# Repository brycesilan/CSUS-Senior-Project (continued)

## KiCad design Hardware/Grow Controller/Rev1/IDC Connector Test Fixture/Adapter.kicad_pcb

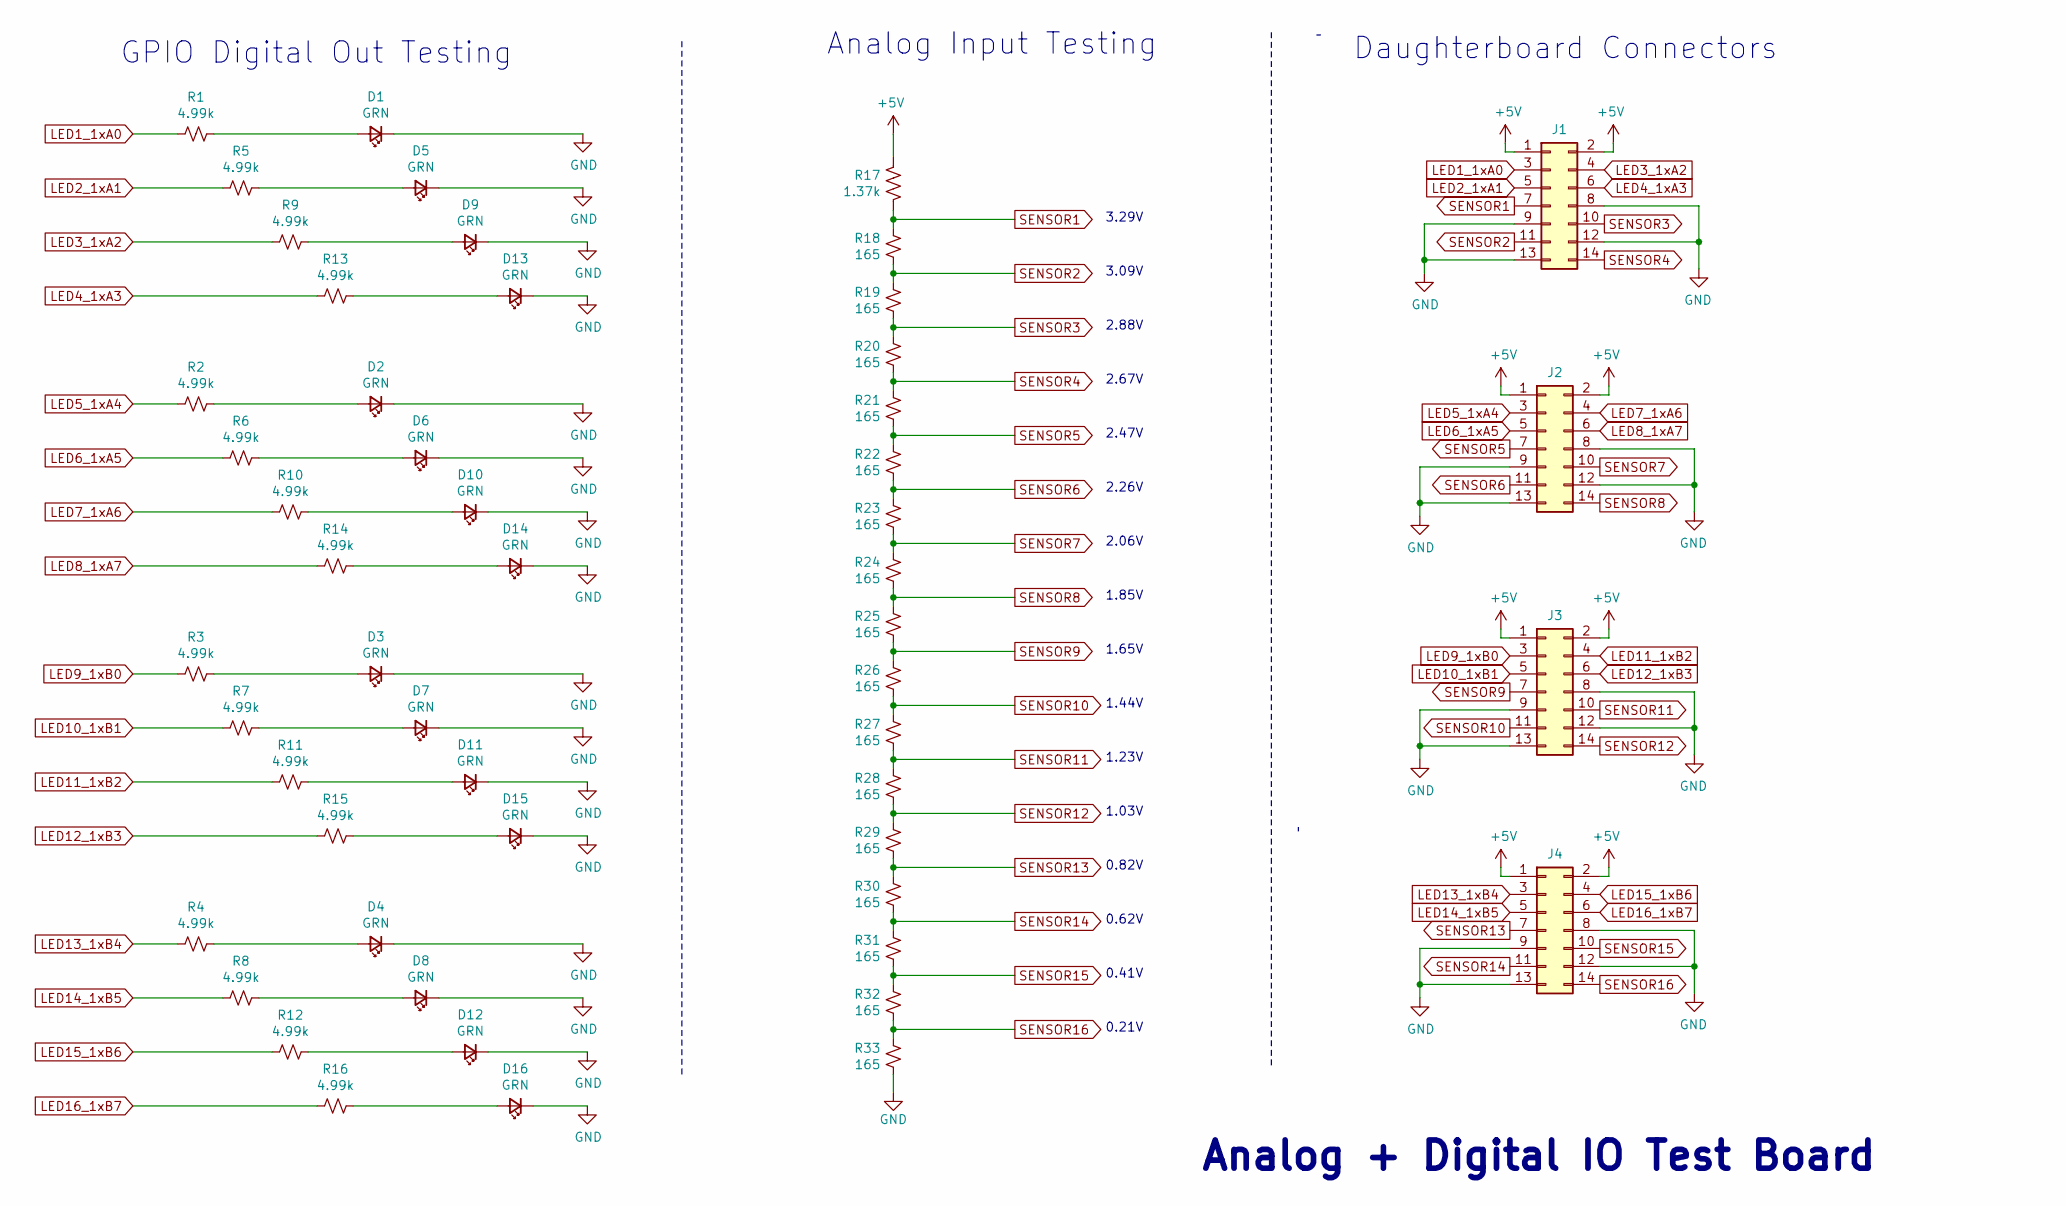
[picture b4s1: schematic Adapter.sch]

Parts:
D1, D2, D3, D4, D5, D6, D7, D8, D9, D10, D11, D12, D13, D14, D15, D16: GRN; D_0603_1608Metric
J1, J2, J3, J4: Conn_02x07_Odd_Even; PinHeader_2x07_P2.54mm_Vertical
R1, R2, R3, R4, R5, R6, R7, R8, R9, R10, R11, R12, R13, R14, R15, R16: 4.99k; R_0603_1608Metric
R17: 1.37k; R_0603_1608Metric
R18, R19, R20, R21, R22, R23, R24, R25, R26, R27, R28, R29, R30, R31, R32, R33: 165; R_0603_1608Metric

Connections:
+5V: J1.1, J1.2, J2.1, J2.2, J3.1, J3.2, J4.1, J4.2, R17.1
GND: D1.1 (K), D2.1 (K), D3.1 (K), D4.1 (K), D5.1 (K), D6.1 (K), D7.1 (K), D8.1 (K), D9.1 (K), D10.1 (K), D11.1 (K), D12.1 (K), D13.1 (K), D14.1 (K), D15.1 (K), D16.1 (K), J1.8, J1.9, J1.12, J1.13, J2.8, J2.9, J2.12, J2.13, J3.8, J3.9, J3.12, J3.13, J4.8, J4.9, J4.12, J4.13, R33.2
LED1_1xA0: J1.3, R1.2
LED2_1xA1: J1.5, R5.2
LED3_1xA2: J1.4, R9.2
LED4_1xA3: J1.6, R13.2
LED5_1xA4: J2.3, R2.2
LED6_1xA5: J2.5, R6.2
LED7_1xA6: J2.4, R10.2
LED8_1xA7: J2.6, R14.2
LED9_1xB0: J3.3, R3.2
LED10_1xB1: J3.5, R7.2
LED11_1xB2: J3.4, R11.2
LED12_1xB3: J3.6, R15.2
LED13_1xB4: J4.3, R4.2
LED14_1xB5: J4.5, R8.2
LED15_1xB6: J4.4, R12.2
LED16_1xB7: J4.6, R16.2
unnamed: D1.2 (A), R1.1
unnamed: D2.2 (A), R2.1
unnamed: D3.2 (A), R3.1
unnamed: D4.2 (A), R4.1
unnamed: D5.2 (A), R5.1
unnamed: D6.2 (A), R6.1
unnamed: D7.2 (A), R7.1
unnamed: D8.2 (A), R8.1
unnamed: D9.2 (A), R9.1
unnamed: D10.2 (A), R10.1
unnamed: D11.2 (A), R11.1
unnamed: D12.2 (A), R12.1
unnamed: D13.2 (A), R13.1
unnamed: D14.2 (A), R14.1
unnamed: D15.2 (A), R15.1
unnamed: D16.2 (A), R16.1
SENSOR1: J1.7, R17.2, R18.1
SENSOR2: J1.11, R18.2, R19.1
SENSOR3: J1.10, R19.2, R20.1
SENSOR4: J1.14, R20.2, R21.1
SENSOR5: J2.7, R21.2, R22.1
SENSOR6: J2.11, R22.2, R23.1
SENSOR7: J2.10, R23.2, R24.1
SENSOR8: J2.14, R24.2, R25.1
SENSOR9: J3.7, R25.2, R26.1
SENSOR10: J3.11, R26.2, R27.1
SENSOR11: J3.10, R27.2, R28.1
SENSOR12: J3.14, R28.2, R29.1
SENSOR13: J4.7, R29.2, R30.1
SENSOR14: J4.11, R30.2, R31.1
SENSOR15: J4.10, R31.2, R32.1
SENSOR16: J4.14, R32.2, R33.1

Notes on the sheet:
Daughterboard Connectors
GPIO Digital Out Testing
Analog Input Testing
3.09V
3.29V
2.88V
2.67V
2.47V
2.26V
1.85V
2.06V
1.65V
1.44V
1.23V
1.03V
0.62V
0.82V
0.41V
0.21V
Analog + Digital IO Test Board

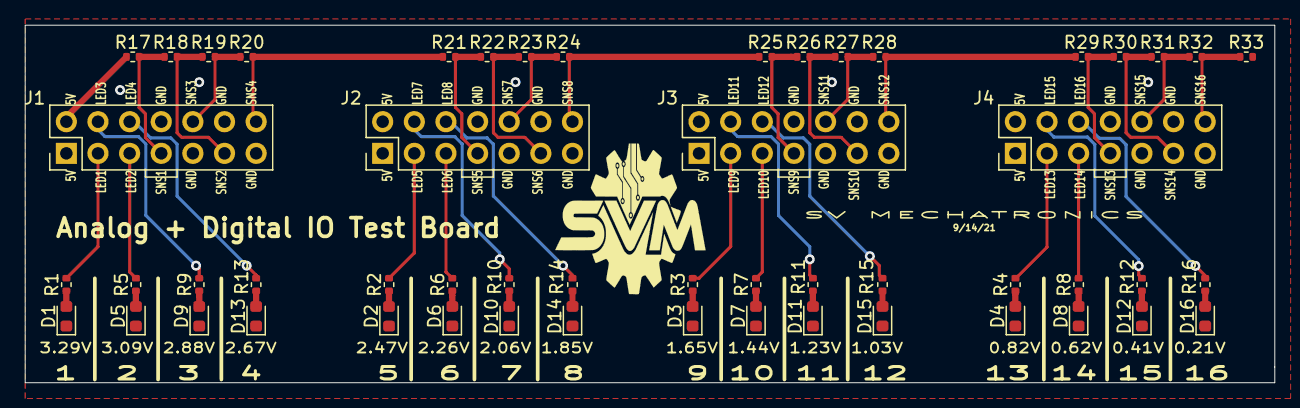
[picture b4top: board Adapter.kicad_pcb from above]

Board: 2 copper layers, 100.3 x 28.7 mm, 53 parts (0 on the bottom side), 50 nets.

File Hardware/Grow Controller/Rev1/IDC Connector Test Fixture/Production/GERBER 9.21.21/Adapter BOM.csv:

Comment,Designator,Footprint,LCSC Part Number
Green LED_0603,"D1,D2,D3,D4,D5,D6,D7,D8,D9,D10,D11,D12,D13,D14,D15,D16",D_0603,
4.99k,"R1,R2,R3,R4,R5,R6,R7,R8,R9,R10,R11,R12,R13,R14,R15,R16",R_0603,
1.37k,R17,R_0603,
165,"R18,R19,R20,R21,R22,R23,R24,R25,R26,R27,R28,R29,R30,R31,R32,R33",R_0603,

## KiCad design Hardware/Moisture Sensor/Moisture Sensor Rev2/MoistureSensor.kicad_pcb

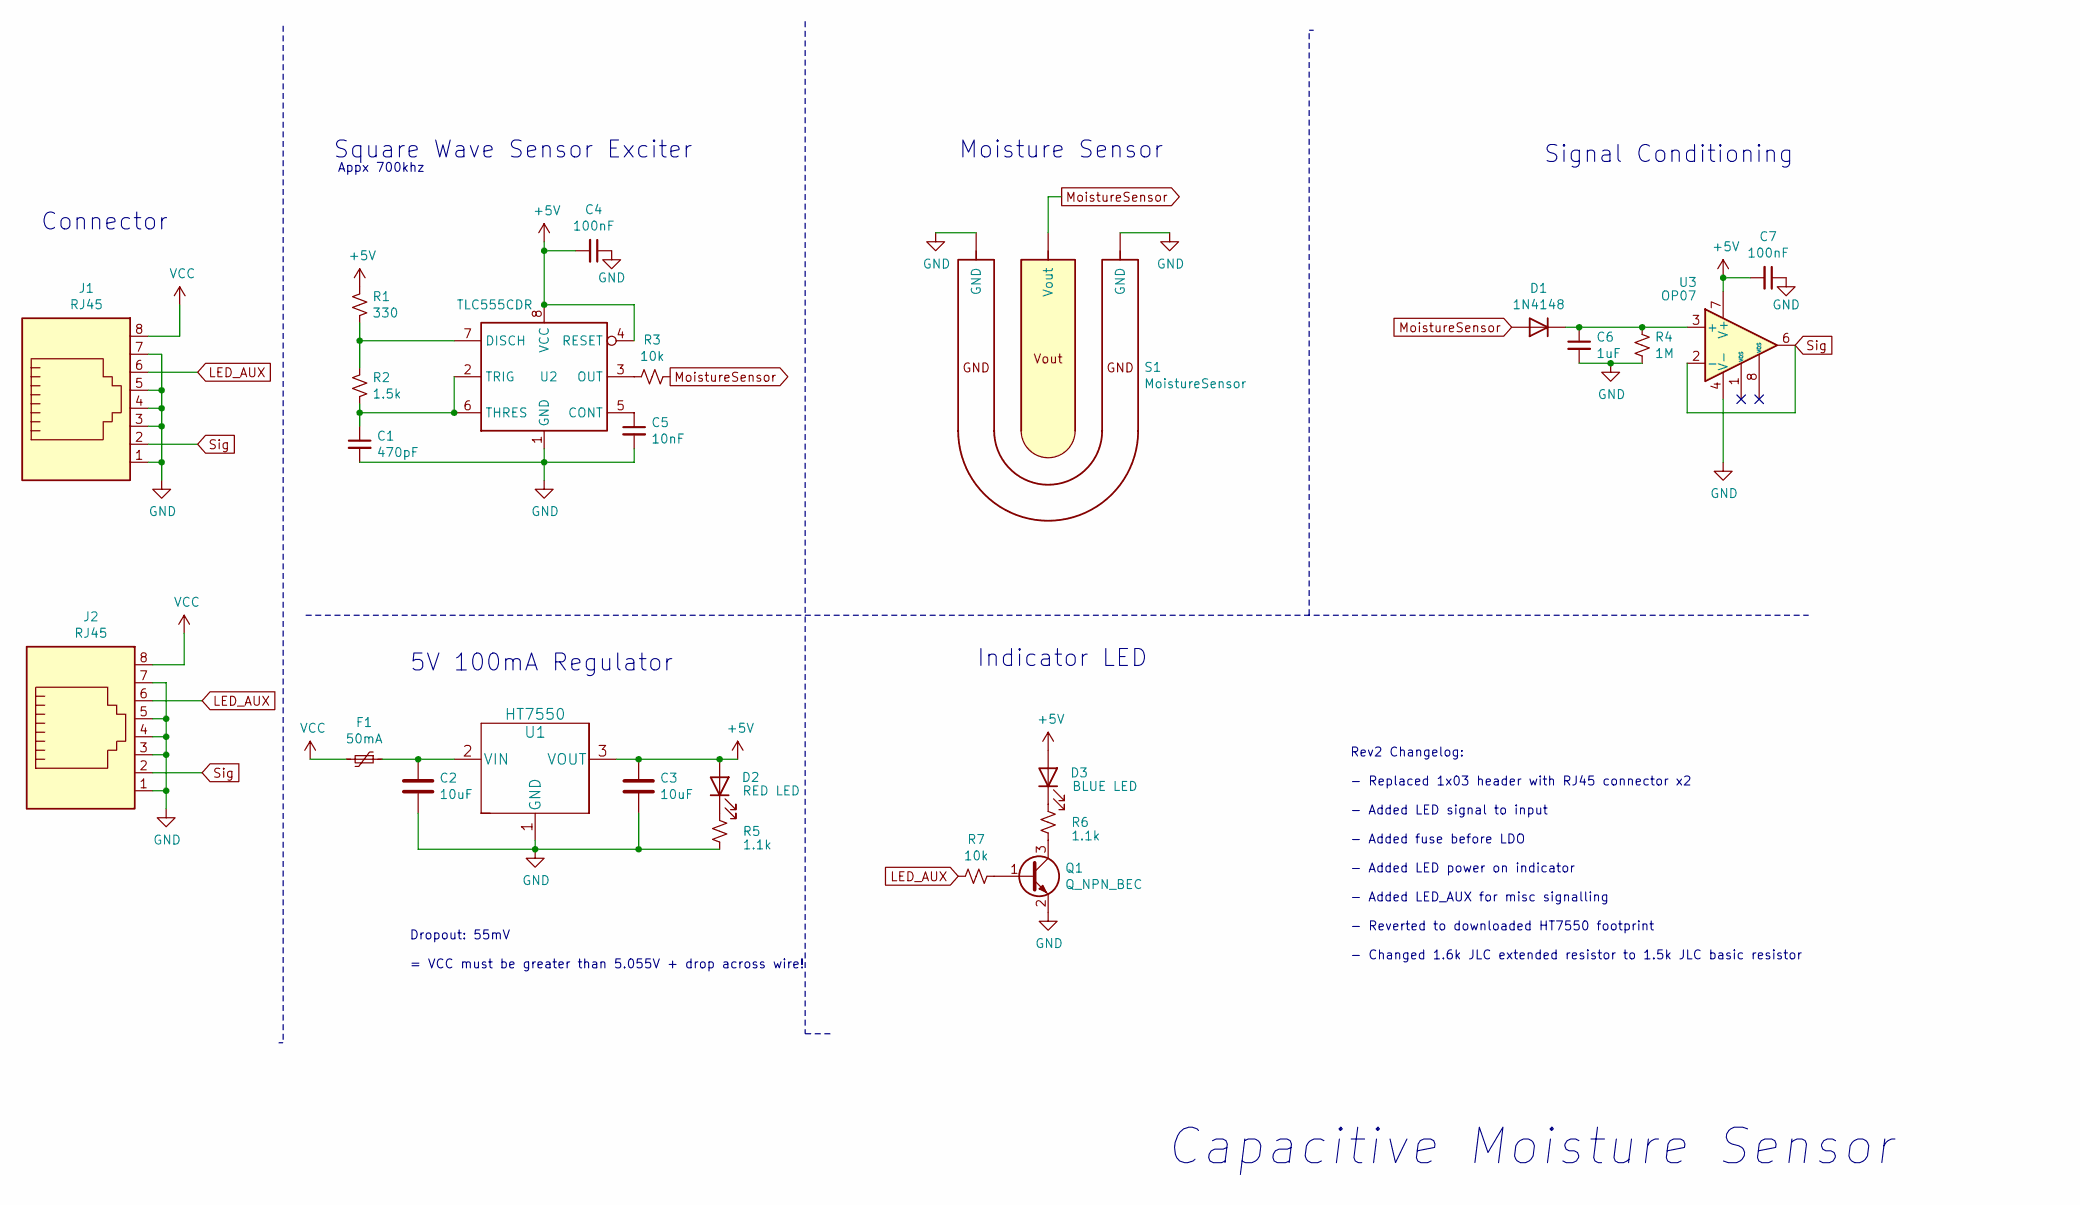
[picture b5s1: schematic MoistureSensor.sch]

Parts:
C1: 470pF; C_0402_1005Metric
C2, C3: 10uF; C_0805_2012Metric
C4, C7: 100nF; C_0402_1005Metric
C5: 10nF; C_0402_1005Metric
C6: 1uF; C_0603_1608Metric
D1: 1N4148; D_SOD-323F
D2: RED LED; LED_0805_2012Metric
D3: BLUE LED; LED_0805_2012Metric
F1: 50mA; Fuse_1206_3216Metric
J1, J2: RJ45; AMPHENOL_54602-908LF
Q1: Q_NPN_BEC; SOT-23
R1: 330; R_0402_1005Metric
R2: 1.5k; R_0402_1005Metric
R3, R7: 10k; R_0402_1005Metric
R4: 1M; R_0402_1005Metric
R5, R6: 1.1k; R_0603_1608Metric
S1: MoistureSensor
U1: HT7550; HT7550-1-SOT89TRLF
U2: TLC555CDR; SOIC-8_3.9x4.9mm_P1.27mm
U3: OP07; SOIC-8_3.9x4.9mm_P1.27mm

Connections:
+5V: C3.1, C4.2, C7.2, D2.2 (A), D3.2 (A), R1.1, U1.3 (VOUT), U2.4 (RESET), U2.8 (VCC), U3.7 (V+)
GND: C1.2, C2.2, C3.2, C4.1, C5.2, C6.2, C7.1, J1.1, J1.3, J1.4, J1.5, J1.7, J2.1, J2.3, J2.4, J2.5, J2.7, Q1.2 (E), R4.2, R5.2, S1.1 (GND), S1.3 (GND), U1.1 (GND), U2.1 (GND), U3.4 (V-)
LED_AUX: J1.6, J2.6, R7.2
MoistureSensor: D1.2 (A), R3.1, S1.2 (Vout)
unnamed: C1.1, R2.2, U2.2 (TRIG), U2.6 (THRES)
unnamed: C2.1, F1.1, U1.2 (VIN)
unnamed: C5.1, U2.5 (CONT)
unnamed: C6.1, D1.1 (K), R4.1, U3.3 (+)
unnamed: D2.1 (K), R5.1
unnamed: D3.1 (K), R6.1
unnamed: Q1.1 (B), R7.1
unnamed: Q1.3 (C), R6.2
unnamed: R1.2, R2.1, U2.7 (DISCH)
unnamed: R3.2, U2.3 (OUT)
Sig: J1.2, J2.2, U3.2 (-), U3.6
VCC: F1.2, J1.8, J2.8

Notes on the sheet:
Appx 700khz
Square Wave Sensor Exciter
Moisture Sensor
Signal Conditioning
5V 100mA Regulator
Connector
Dropout: 55mV = VCC must be greater than 5.055V + drop across wire!
Rev2 Changelog: - Replaced 1x03 header with RJ45 connector x2 - Added LED signal to input - Added fuse before LDO - Added LED power on indicator - Added LED_AUX for misc signalling - Reverted to downloaded HT7550 footprint - Changed 1.6k JLC extended resistor to 1.5k JLC basic resistor
Indicator LED
Capacitive Moisture Sensor

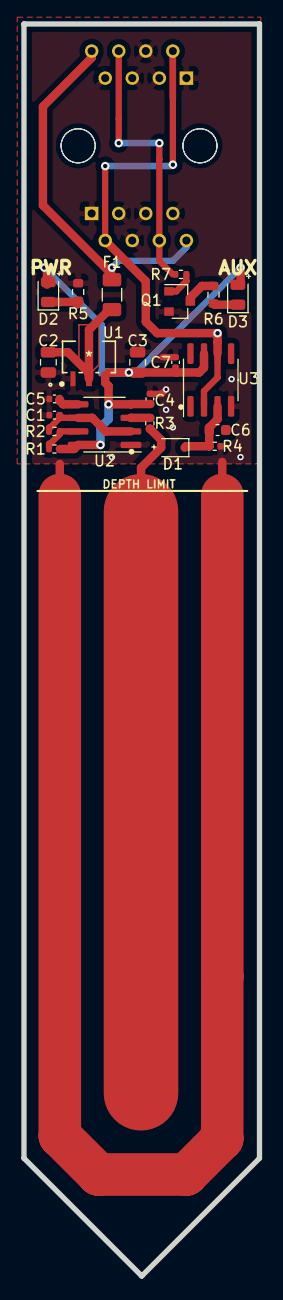
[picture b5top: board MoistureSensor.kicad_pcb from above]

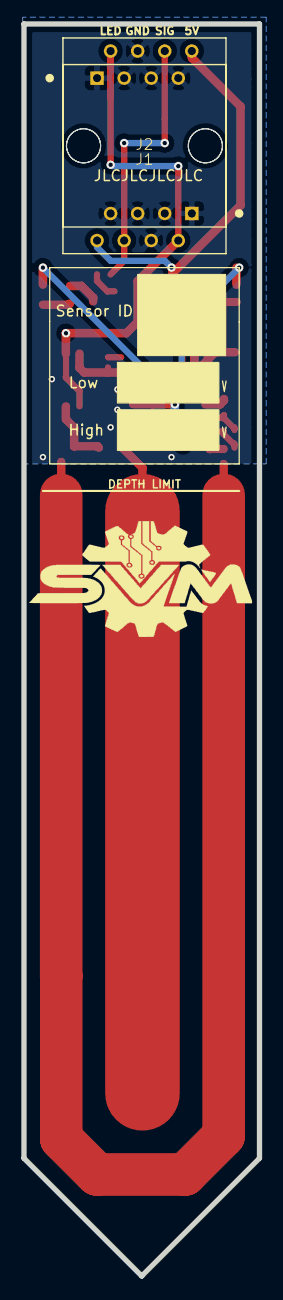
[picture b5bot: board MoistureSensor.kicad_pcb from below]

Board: 2 copper layers, 22.1 x 117.5 mm, 24 parts (2 on the bottom side), 16 nets.

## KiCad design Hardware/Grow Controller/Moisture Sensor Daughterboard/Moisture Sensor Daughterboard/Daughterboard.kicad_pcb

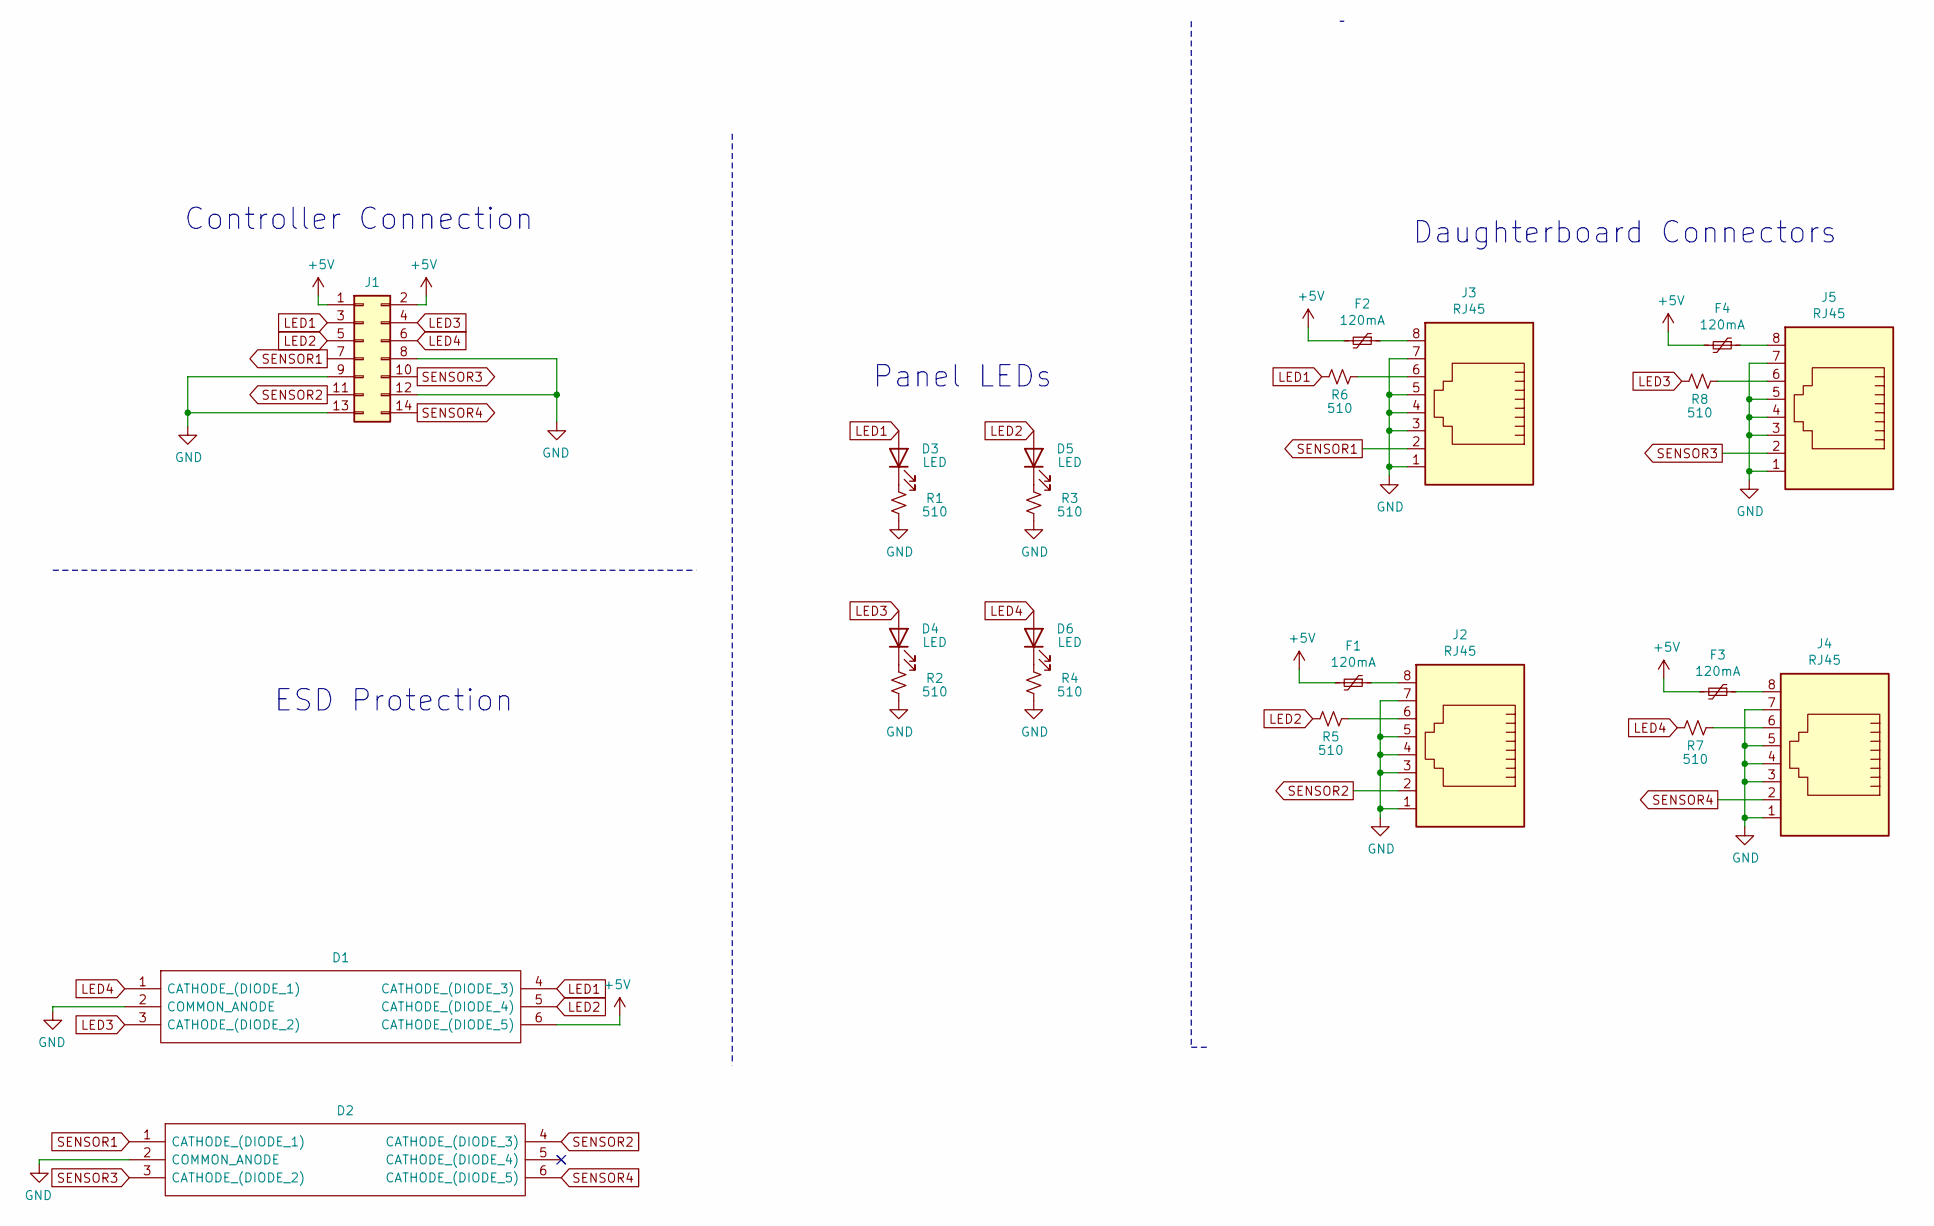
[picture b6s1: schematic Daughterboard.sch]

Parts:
D1, D2: PESD5V0L5UV,115; SOTFL50P160X60-6N; Manufacturer_Part_Number PESD5V0L5UV,115; Mouser Part Number 771-PESD5V0L5UV115
D3, D4, D5, D6: LED; LED_0805_2012Metric
F1, F2, F3, F4: 120mA; Fuse_0603_1608Metric_Pad1.05x0.95mm_HandSolder
J1: Conn_02x07_Odd_Even; IDC-Header_2x07_P2.54mm_Latch_Vertical
J2, J3, J4, J5: RJ45; RJ45_OST_PJ012-8P8CX_Vertical
R1, R2, R3, R4, R5, R6, R7, R8: 510; R_0805_2012Metric

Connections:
+5V: D1.6 (CATHODE_(DIODE_5)), F1.2, F2.2, F3.2, F4.2, J1.1, J1.2
GND: D1.2 (COMMON_ANODE), D2.2 (COMMON_ANODE), J1.8, J1.9, J1.12, J1.13, J2.1, J2.3, J2.4, J2.5, J2.7, J3.1, J3.3, J3.4, J3.5, J3.7, J4.1, J4.3, J4.4, J4.5, J4.7, J5.1, J5.3, J5.4, J5.5, J5.7, R1.1, R2.1, R3.1, R4.1
LED1: D1.4 (CATHODE_(DIODE_3)), D3.2 (A), J1.3, R6.2
LED2: D1.5 (CATHODE_(DIODE_4)), D5.2 (A), J1.5, R5.2
LED3: D1.3 (CATHODE_(DIODE_2)), D4.2 (A), J1.4, R8.2
LED4: D1.1 (CATHODE_(DIODE_1)), D6.2 (A), J1.6, R7.2
unnamed: D3.1 (K), R1.2
unnamed: D4.1 (K), R2.2
unnamed: D5.1 (K), R3.2
unnamed: D6.1 (K), R4.2
unnamed: F1.1, J2.8
unnamed: F2.1, J3.8
unnamed: F3.1, J4.8
unnamed: F4.1, J5.8
unnamed: J2.6, R5.1
unnamed: J3.6, R6.1
unnamed: J4.6, R7.1
unnamed: J5.6, R8.1
SENSOR1: D2.1 (CATHODE_(DIODE_1)), J1.7, J3.2
SENSOR2: D2.4 (CATHODE_(DIODE_3)), J1.11, J2.2
SENSOR3: D2.3 (CATHODE_(DIODE_2)), J1.10, J5.2
SENSOR4: D2.6 (CATHODE_(DIODE_5)), J1.14, J4.2

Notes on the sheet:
Daughterboard Connectors
Controller Connection
Panel LEDs
ESD Protection

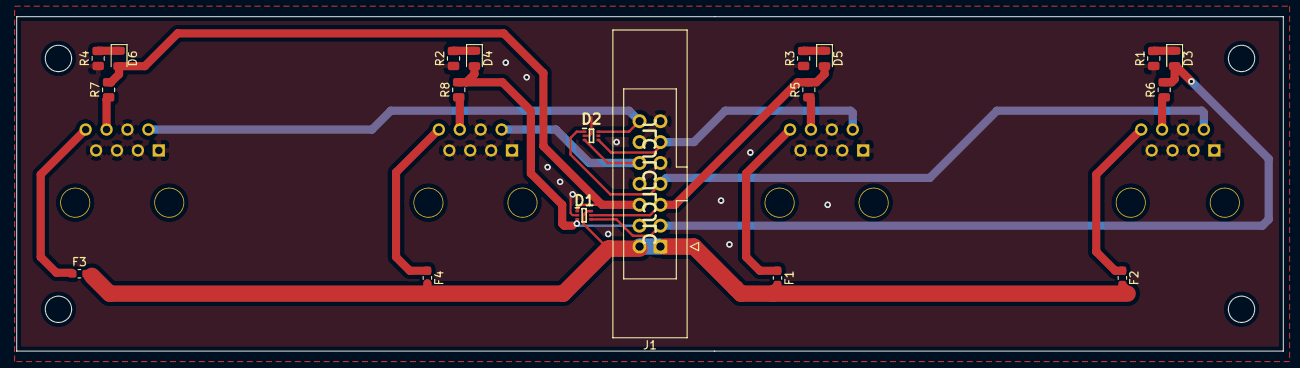
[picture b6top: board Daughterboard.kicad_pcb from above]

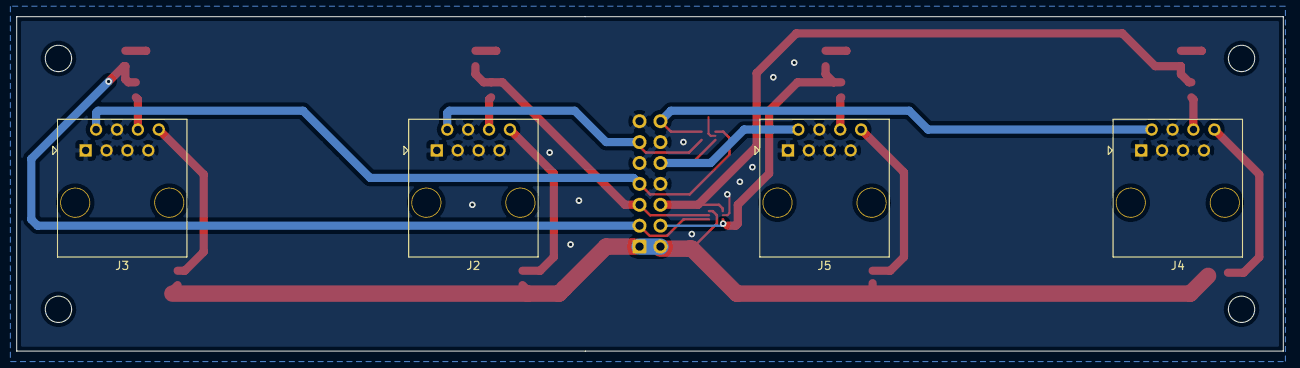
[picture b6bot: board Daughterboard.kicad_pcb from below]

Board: 2 copper layers, 153.9 x 40.6 mm, 23 parts (4 on the bottom side), 22 nets.

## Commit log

2022-03-20 First iteration of hardware designs
2022-04-12 Add working index.html
2022-04-13 Update with single button requesting multiple sensor readings
2022-04-22 Add Moisture and pH sensor Arduino Code
2022-04-22 Correct pH sensor Arduino code
2022-04-22 Hardware updates
2022-04-26 separate temperature,ph functions and add water control to index.html
2022-04-26 Code cleanup and add timer to check main function runtime
2022-04-26 pH and moisture code, initial complete working version
2022-04-27 Modify app.py to read moisture and ph from the same Arduino
2022-05-05 change html files for UI
2022-05-05 add comments, code cleanup in app.py. color change in index.html
2022-05-06 Add timestamps to app.py and index.html
2022-05-06 Add data logging capability to app.py
2022-05-06 Added relay control
2022-05-06 Combined pH + Moisture + RPi interface
2022-05-06 Add auto-refresh functionality
2022-05-06 Add pin configurations
2022-05-06 Incomplete working code with light control
2022-05-07 Light and water working
2022-05-07 Code cleanup and working
2022-05-11 Change to 'Get sensor readings'
2022-05-11 Correct pH calibration values
2022-07-24 Correct spelling error in README.md
2022-08-02 Added Control_Board
2022-09-18 Control board updates
2022-09-18 Sch rev 1 ready for review
2022-09-18 Cleaned up hardware repo
2022-09-19 Control board layout
2022-10-06 Move semester 1 software to Software-sem1 folder
2022-10-06 Update README.md for Software directory
2022-10-09 PCB layout additions
2022-10-09 PCB layout updates
2022-10-13 Control_Board updates
2022-10-19 Board updates, ready for power regulation component placements
2022-10-20 Laid out power regulation stuffs
2022-10-24 10_23_2022_3_pin_headers
2022-10-25 Updated Analog sensor routing
2022-10-25 v0.1 Ready for review
2022-10-25 Vertical fix
2022-10-25 Schematic hotfix
2022-10-26 v0.1 Gerbers
2022-10-26 initial setup
2022-10-30 Update Arduino code to use 4 moisture sensors (not tested)
2022-11-02 Move Moisture_pH.ino to Arduino/
2022-11-14 pH and moisture1 working
2022-11-14 Remove unnecessary serial prints
2022-11-14 fix argument
2022-11-15 Sensor read working
2022-11-16 create Reading object after reading from sensors
2022-11-18 Initialize react app and tailwind css
2022-11-18 Create pages and routes
2022-11-18 Complete header
2022-11-18 Complete design for sign-in, sign-up, forgot-password
2022-11-19 Apply Prettier formatting to pages and components
2022-11-19 handle react-scripts vulnerability
2022-11-19 Complete SignIn, SignUp, ForgotPassword functionality
2022-11-19 Create PrivateRoute and useAuthState hook
2022-11-19 Change name functionality complete
2022-11-19 Make header dynamic profile/sign-in
2022-11-19 Add Spinner component
2022-11-20 Add date, correct serial read
2022-11-20 Untrack some /node_modules subfolders
2022-11-20 test
2022-11-20 Changed all import to CommonJS requires
2022-11-21 Add flowing LED test script to test RPi GPIO
2022-11-22 Basic write to firestore working
2022-11-26 Push values to firestore Current and daily document working
2022-11-27 Code save before connecting to 120VaC
2022-11-27 Add gpio code
2022-12-02 Multiple edits and add README to sem1 software
2022-12-04 Add settings to Home.jsx, signUp.jsx
2022-12-04 Add hard-coded settings to profile.jsx
2022-12-04 Change graph colors
2022-12-05 Change logo, update profile
2022-12-05 Automation and buttons working
2022-12-09 Change Logo
2022-12-13 Add comments and update Graphs.jsx
2022-12-13 Add comments to Client code
2022-12-13 Fix links
2022-12-13 Add screenshots to sem 2 and sem 1 folders
